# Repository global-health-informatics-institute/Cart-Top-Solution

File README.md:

# Cart-Top-Solution
Circuit board design
&
Fusion 3D design

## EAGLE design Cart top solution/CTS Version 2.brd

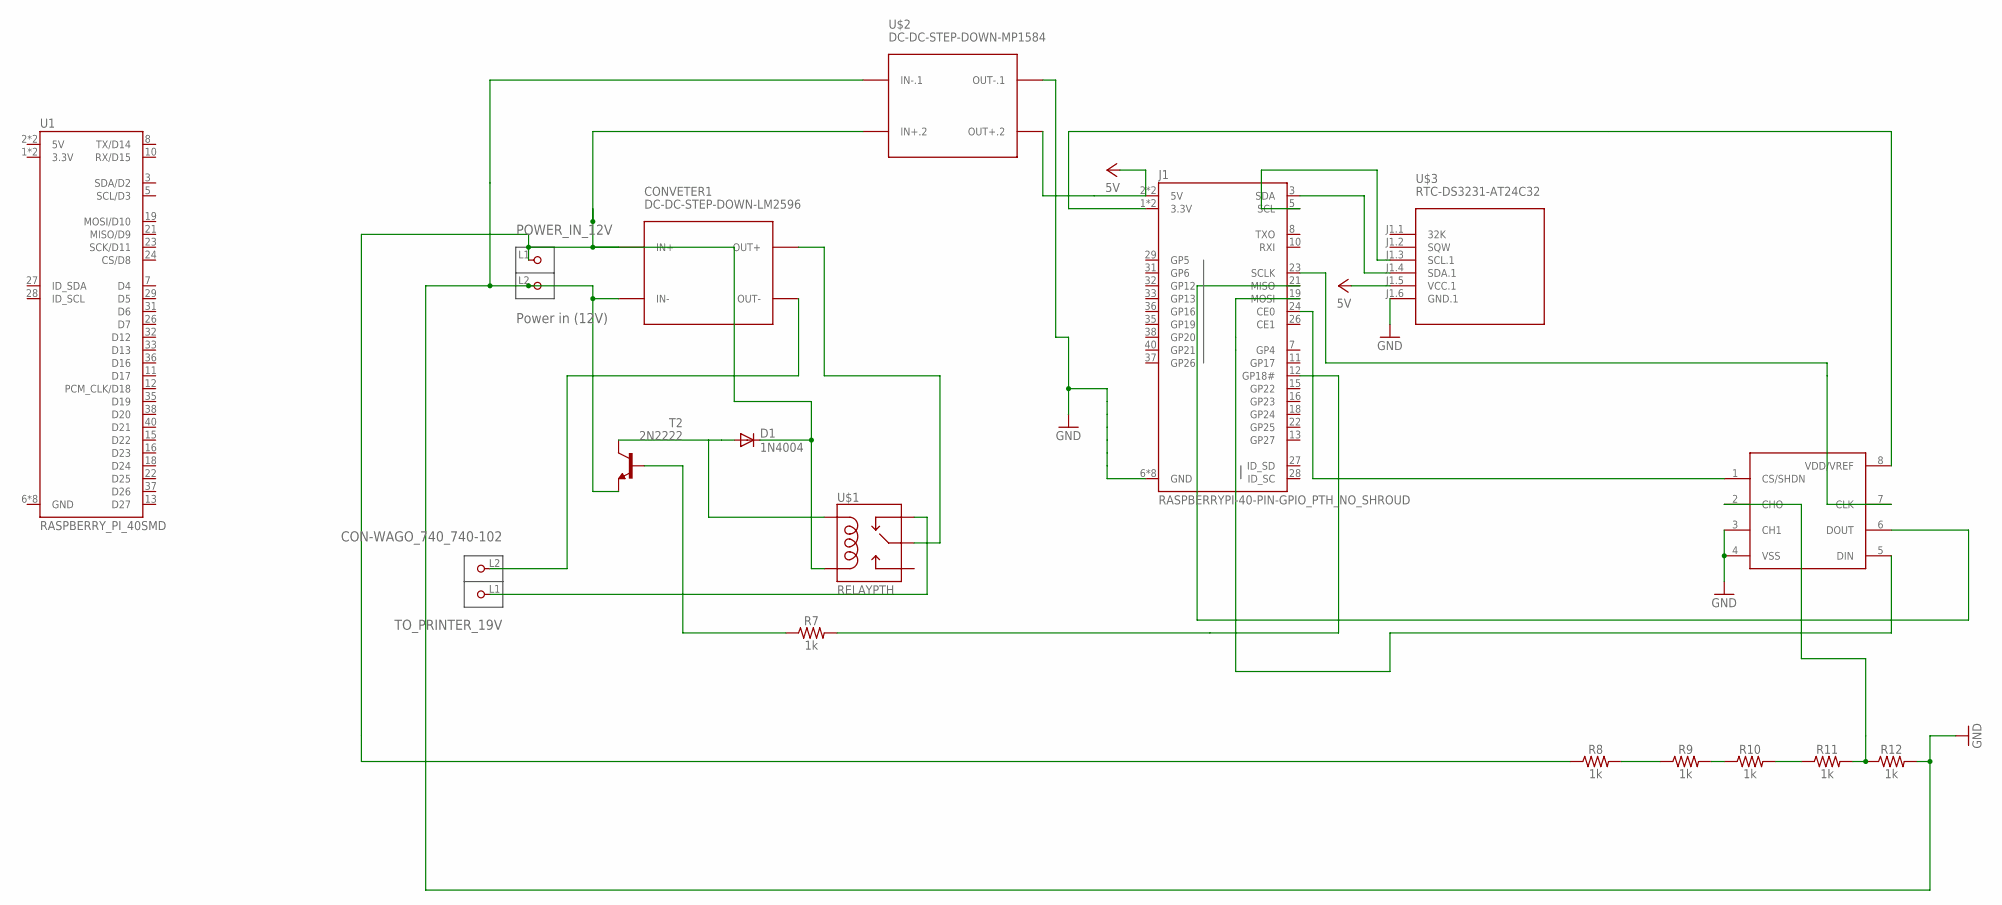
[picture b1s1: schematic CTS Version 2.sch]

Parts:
CONVETER1: DC-DC-STEP-DOWN-LM2596
D1: 1N4004; DO41-10
DPI1: DIP762W53P254L900H508Q8B'; SOP254P1132X265-8N
J1: RASPBERRYPI-40-PIN-GPIO_PTH_NO_SHROUD; 2X20
POWER_IN_12V: Power in (12V); CON-WAGO_740_P-740-102
R7, R8, R9, R10, R11, R12: 1k; AXIAL-0.3
T2: 2N2222; TO92-EBC-OVAL
TO_PRINTER_19V: CON-WAGO_740_740-102; CON-WAGO_740_P-740-102
U1: RASPBERRY_PI_40SMD; RASPBERRY_PI_SHIELD_HOLES
U$1: RELAYPTH; SRD-05VDC-SL-C
U$2: DC-DC-STEP-DOWN-MP1584
U$3: RTC-DS3231-AT24C32

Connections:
GND: CONVETER1.IN-, DPI1.3 (CH1), DPI1.4 (VSS), J1.6 (GND), J1.9 (GND), J1.14 (GND), J1.20 (GND), J1.25 (GND), J1.30 (GND), J1.34 (GND), J1.39 (GND), POWER_IN_12V.L2 (P2), R12.P$2 (2), T2.E, U$2.IN-.1, U$2.OUT-.1, U$3.J1.6 (GND.1)
unnamed: CONVETER1.IN+, D1.C, POWER_IN_12V.L1 (P1), R8.P$1 (1), U$1.COIL0, U$2.IN+.2
unnamed: J1.3 (SDA), U$3.J1.4 (SDA.1)
unnamed: DPI1.7 (CLK), J1.23 (SCLK)
unnamed: CONVETER1.OUT-, TO_PRINTER_19V.L2 (P2)
unnamed: R8.P$2 (2), R9.P$1 (1)
unnamed: DPI1.6 (DOUT), J1.21 (MISO)
unnamed: J1.12 (GP18#), R7.P$2 (2)
unnamed: D1.A, T2.C, U$1.COIL1
unnamed: DPI1.5 (DIN), J1.19 (MOSI)
unnamed: DPI1.8 (VDD/VREF), J1.1 (3.3V), J1.17 (3.3V)
unnamed: R7.P$1 (1), T2.B
unnamed: TO_PRINTER_19V.L1 (P1), U$1.SWCLOSED (SWCLOSE)
unnamed: CONVETER1.OUT+, U$1.SWCOMMON
unnamed: DPI1.1 (CS/SHDN), J1.24 (CE0)
unnamed: R9.P$2 (2), R10.P$1 (1)
unnamed: DPI1.2 (CHO), R11.P$2 (2), R12.P$1 (1)
unnamed: R10.P$2 (2), R11.P$1 (1)
unnamed: J1.5 (SCL), U$3.J1.3 (SCL.1)
VCC: J1.2 (5V), J1.4 (5V), U$2.OUT+.2, U$3.J1.5 (VCC.1)

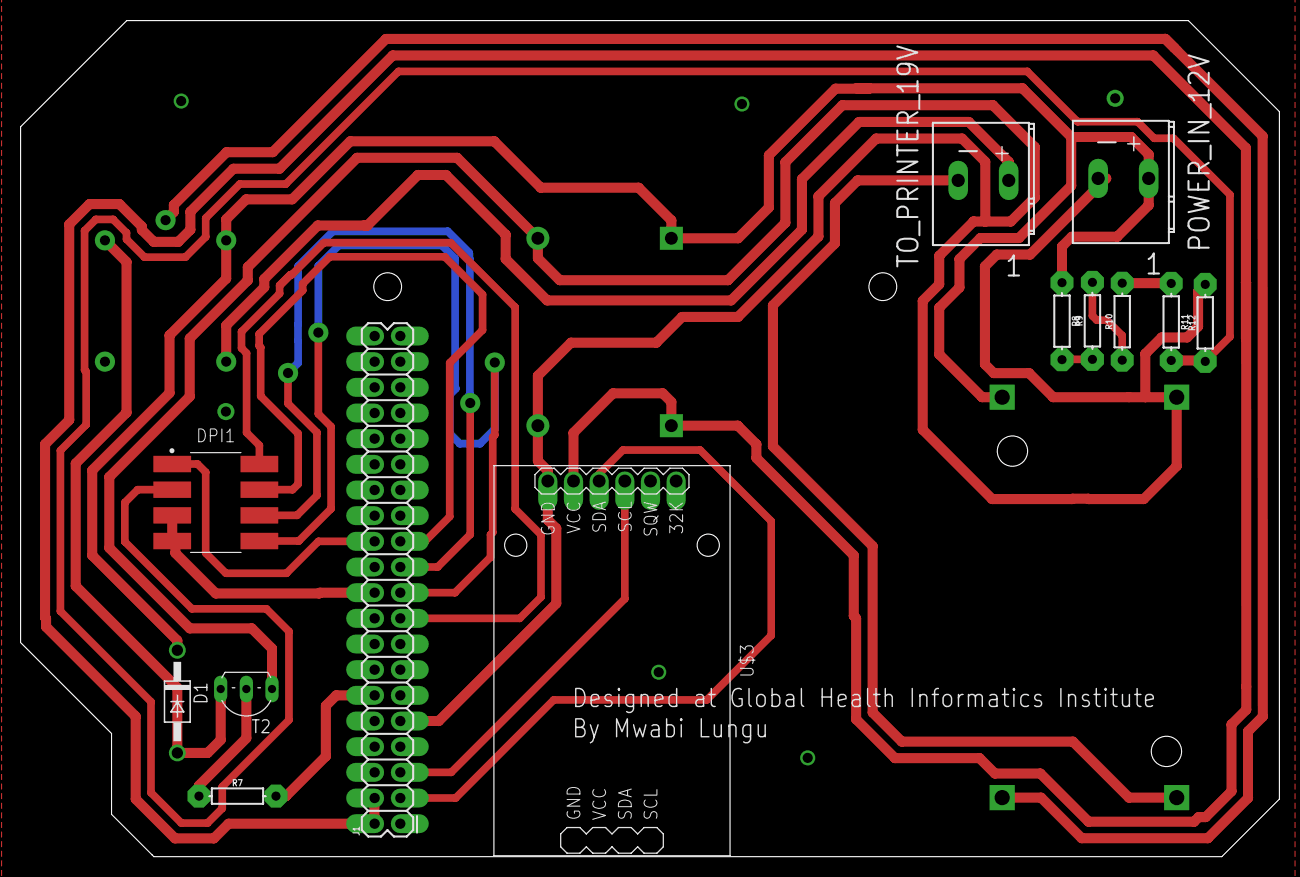
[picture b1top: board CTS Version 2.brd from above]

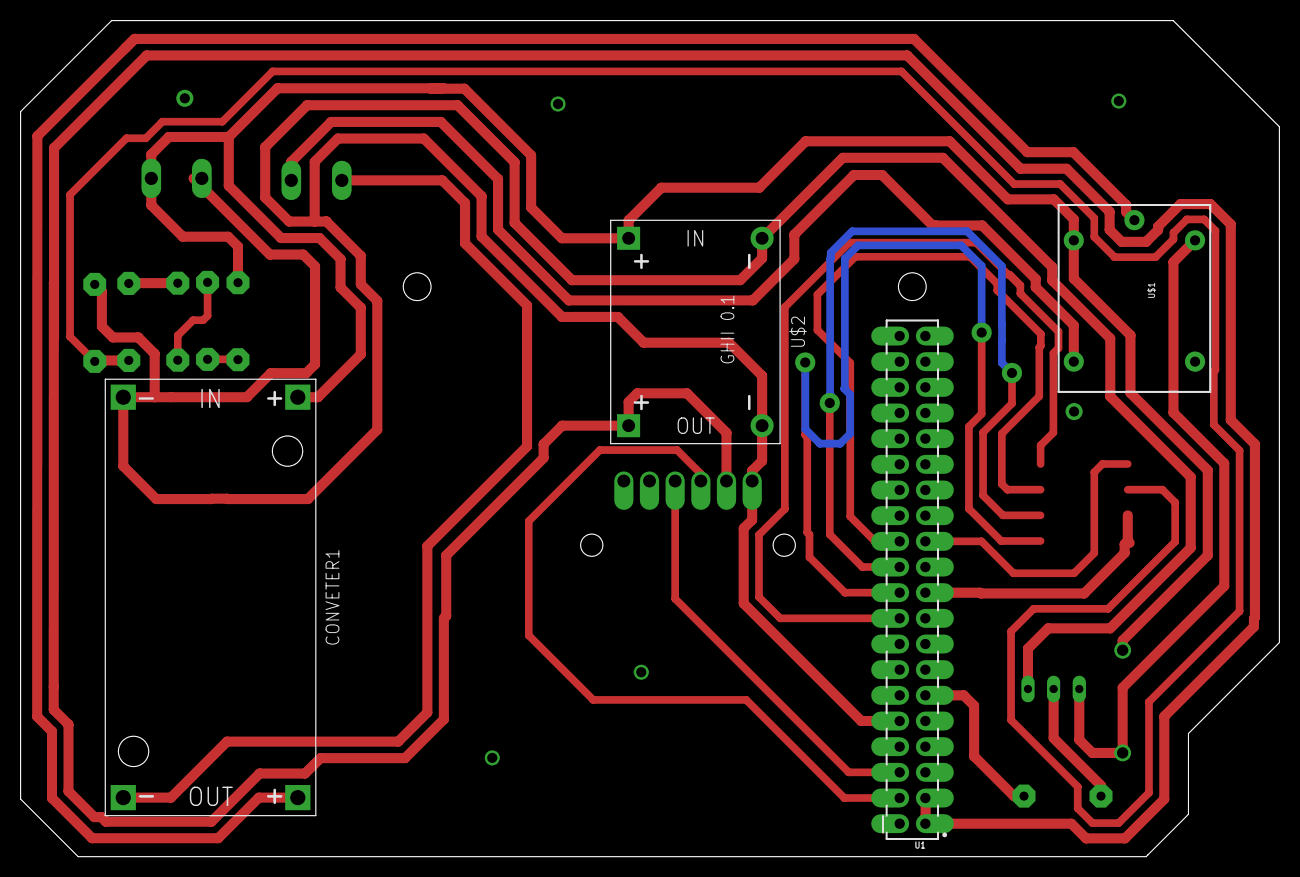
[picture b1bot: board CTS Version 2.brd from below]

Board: 2 copper layers, 124.6 x 82.7 mm, 17 parts (4 on the bottom side), 20 nets.

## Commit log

2019-07-13 Finished circuit board design for the top cart solution
    Designed by Ellie Ng'oma
2019-11-12 Second version with components assembled
2019-11-22 gcodes of GRBL
2019-11-29 Second Version of the Cart top solution circuit board. The updated board has been equiped with a real time clock module
2019-12-04 gcode files
2019-12-10 New version of the carttop solution board with an MCP3002 chip integrated
2019-12-23 2 sided board
2020-01-08 MCP3002 code and library
2020-01-11 Code to control the relay
2020-02-10 Battery monitor with Bars
2020-02-14 python script that helps detect the status of the pin
2020-02-25 new version of the back cover with Docking at the back
2020-02-26 New Version gCodes
2020-03-03 Diode OR circuite
2020-03-04 Adjustable Wall Mount pieces gcodes
2020-03-08 New Docking Station
2020-03-08 gcode file
2020-03-09 Charging monitor via GPIO
2023-01-26 gerber files ready for order
2023-03-30 isolated ground trace from charger

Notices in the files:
parts and their libraries:
GHIdiy-modules: Released under the Creative Commons Attribution 4.0 International License: http://creativecommons.org/licenses/by/4.0
GHIISparkFun-Connectors: Licensing: Creative Commons ShareAlike 4.0 International - https://creativecommons.org/licenses/by-sa/4.0
